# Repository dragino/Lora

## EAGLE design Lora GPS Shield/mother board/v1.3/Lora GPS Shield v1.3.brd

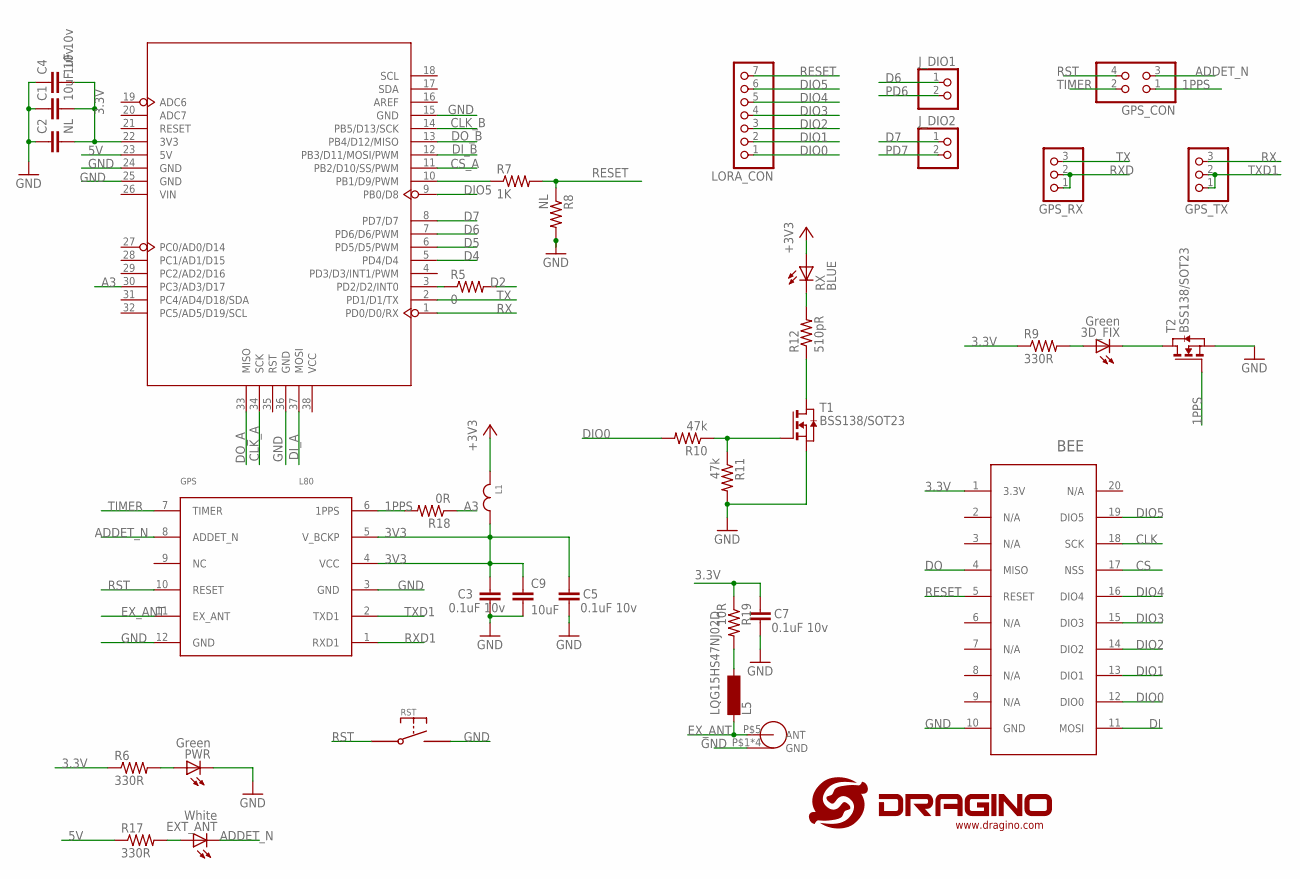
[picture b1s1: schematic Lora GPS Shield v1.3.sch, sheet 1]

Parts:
3D_FIX: Green; CHIPLED_0603
C1: 10uF 10v; C0805
C2: NL; C0402
C3, C5, C7: 0.1uF 10v; C0402
C4: 1uF 10v; C0402
C9: 10uF; C0805
EXT_ANT: White; DRAGINO_CHIPLED_0603
GPS: L80
GPS_ANT: NL; SMA-KE
GPS_CON: PINHD-2X2; 2X02
GPS_RX: PINHD-1X3; 1X03
GPS_TX: PINHD-1X3; 1X03
J_DIO1: PINHD-1X21X2_S; 1X02
J_DIO2: PINHD-1X2; 1X02
L1: JLC-PZ2012D800-3R0TF; C0805
L5: LQG15HS47NJ02D; L-0402
LORA_CON: PINHD-1X71X7_S; 1X07
PWR: Green; DRAGINO_CHIPLED_0603
R5: 0; R0402
R6, R9, R17: 330R; R0402
R7: 1K; R0402
R8: NL; R0402
R10, R11: 47k; R0402
R12: 510pR; R0402
R18: 0R; M0805
R19: 10R; R0402
RST: SWITCHTS-017; TS-017
RX: BLUE; CHIPLED_0603
T1, T2: BSS138/SOT23; SOT-23
U3: BEE; LORA
U5: MOUDLE_ARDUINO-38PMOUDLE_ARDUINO-38P_L; MOUDLE_ARDUINO-38P_L
U$1: LOGO-NEW; LOGO-SILK-NEW

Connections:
1PPS: GPS.6 (1PPS), GPS_CON.1, R18.2, T2.3 (G)
3.3V: C1.2, C2.2, C4.2, C7.2, L1.1, R6.1, R9.1, R19.1, RX.A, U3.1 (3.3V), U5.22 (3V3); also elsewhere on the board
3V3: C3.2, C5.2, C9.1, GPS.4 (VCC), GPS.5 (V_BCKP), L1.2
5V: R17.1, U5.23 (5V)
/RESET: R12.1, T1.1 (D)
A3: R18.1, U5.30 (PC3/AD3/D17)
ADDET_N: EXT_ANT.C, GPS.8 (ADDET_N), GPS_CON.3
CLK: U3.18 (SCK); also elsewhere on the board
CLK_A: U5.34 (SCK); also elsewhere on the board
CLK_B: U5.14 (PB5/D13/SCK); also elsewhere on the board
CS: U3.17 (NSS); also elsewhere on the board
CS_A: U5.11 (PB2/D10/SS/PWM); also elsewhere on the board
D2: R5.2; also elsewhere on the board
D4: U5.5 (PD4/D4); also elsewhere on the board
D5: U5.6 (PD5/D5/PWM); also elsewhere on the board
D6: J_DIO1.1, U5.7 (PD6/D6/PWM)
D7: J_DIO2.1, U5.8 (PD7/D7)
DI: U3.11 (MOSI); also elsewhere on the board
DIO0: LORA_CON.1, R10.2, U3.12 (DIO0); also elsewhere on the board
DIO1: LORA_CON.2, U3.13 (DIO1); also elsewhere on the board
DIO2: LORA_CON.3, U3.14 (DIO2); also elsewhere on the board
DIO3: LORA_CON.4, U3.15 (DIO3)
DIO4: LORA_CON.5, U3.16 (DIO4)
DIO5: LORA_CON.6, U3.19 (DIO5), U5.9 (PB0/D8)
DI_A: U5.37 (MOSI); also elsewhere on the board
DI_B: U5.12 (PB3/D11/MOSI/PWM); also elsewhere on the board
DO: U3.4 (MISO); also elsewhere on the board
DO_A: U5.33 (MISO); also elsewhere on the board
DO_B: U5.13 (PB4/D12/MISO); also elsewhere on the board
EX_ANT: GPS.11 (EX_ANT), GPS_ANT.P$5 (ANT), L5.1
GND: C1.1, C2.1, C3.1, C4.1, C5.1, C7.1, C9.2, GPS.3 (GND), GPS.12 (GND), GPS_ANT.P$1 (GND), GPS_ANT.P$2 (GND), GPS_ANT.P$3 (GND), GPS_ANT.P$4 (GND), PWR.C, R8.2, R11.2, RST.P$2, T1.2 (S), T2.2 (S), U3.10 (GND), U5.15 (GND), U5.24 (GND), U5.25 (GND), U5.36 (GND); also elsewhere on the board
unnamed: R5.1, U5.3 (PD2/D2/INT0)
unnamed: PWR.A, R6.2
unnamed: R7.1, U5.10 (PB1/D9/PWM)
unnamed: 3D_FIX.A, R9.2
unnamed: 3D_FIX.C, T2.1 (D)
unnamed: R10.1, R11.1, T1.3 (G)
unnamed: EXT_ANT.A, R17.2
unnamed: L5.2, R19.2
unnamed: R12.2, RX.C
PD6: J_DIO1.2; also elsewhere on the board
PD7: J_DIO2.2; also elsewhere on the board
RESET: LORA_CON.7, R7.2, R8.1, U3.5 (RESET)
RST: GPS.10 (RESET), GPS_CON.4, RST.P$1
RX: GPS_TX.3, U5.1 (PD0/D0/RX)
RXD: GPS_RX.1, GPS_RX.2; also elsewhere on the board
RXD1: GPS.1 (RXD1); also elsewhere on the board
TIMER: GPS.7 (TIMER), GPS_CON.2
TX: GPS_RX.3, U5.2 (PD1/D1/TX)
TXD1: GPS.2 (TXD1), GPS_TX.1, GPS_TX.2

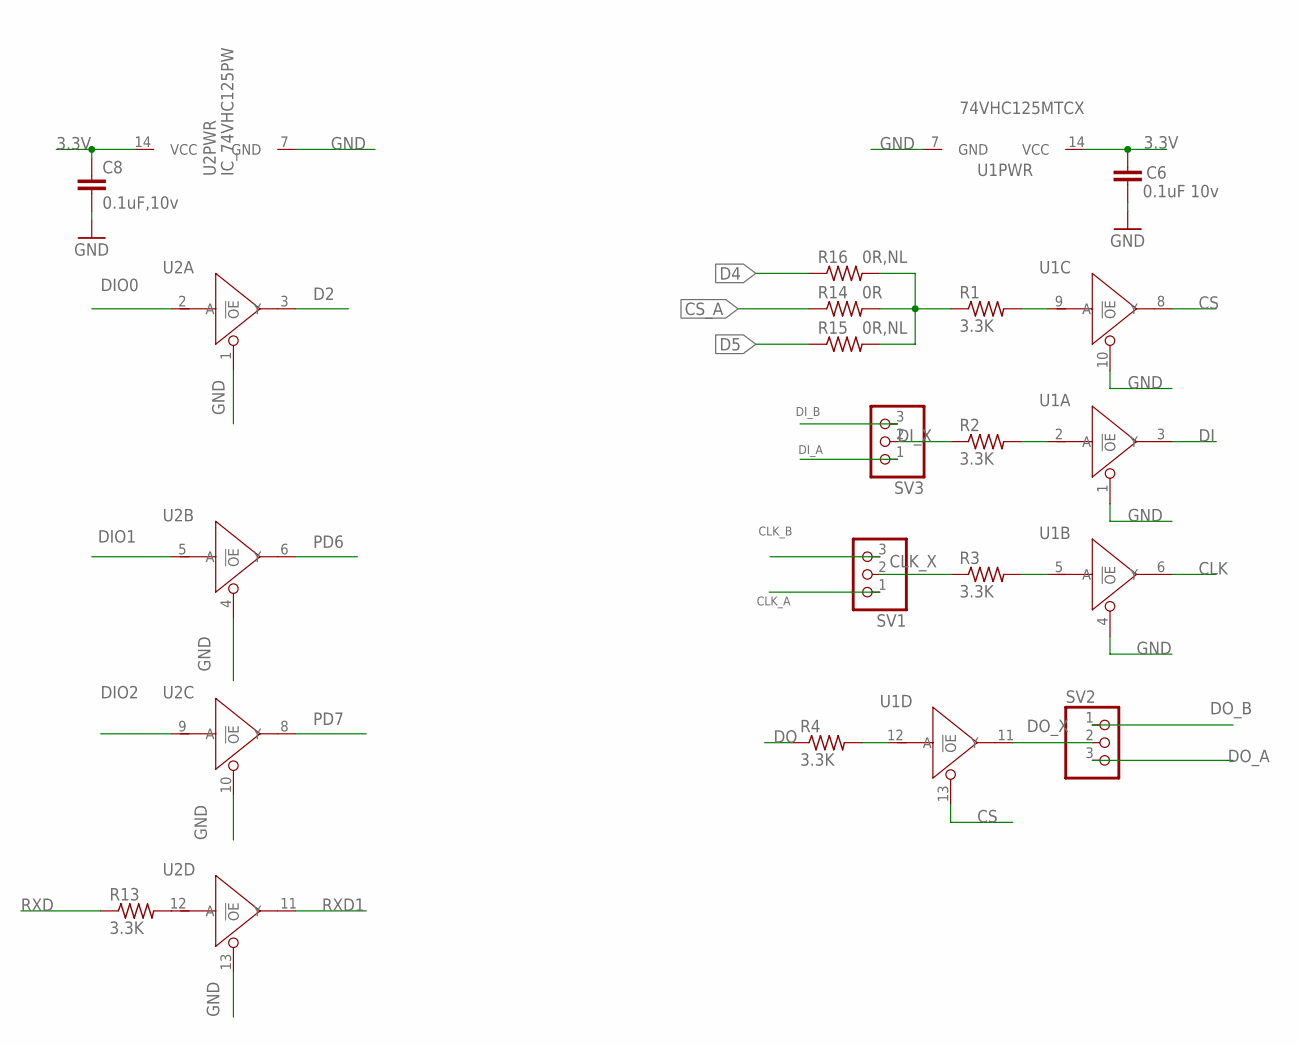
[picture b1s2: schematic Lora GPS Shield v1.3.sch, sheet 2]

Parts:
C6: 0.1uF 10v; C0402
C8: 0.1uF,10v; C0402
R1, R2, R3, R4, R13: 3.3K; R0402
R14: 0R; R0603
R15, R16: 0R,NL; R0603
SV1: PINHD-1X31X3_S; 1X03
SV2, SV3: PINHD-1X3; 1X03
U1: 74VHC125MTCX; TSSOP14
U2: IC_74VHC125PW; IC_TSSOP14

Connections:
3.3V: C6.2, C8.1, U1.14 (VCC), U2.14 (VCC); also elsewhere on the board
CLK: U1.6 (Y); also elsewhere on the board
CLK_A: SV1.1; also elsewhere on the board
CLK_B: SV1.3; also elsewhere on the board
CLK_X: R3.1, SV1.2
CS: U1.8 (Y), U1.13 (!OE); also elsewhere on the board
CS_A: R14.1; also elsewhere on the board
D2: U2.3 (Y); also elsewhere on the board
D4: R16.1; also elsewhere on the board
D5: R15.1; also elsewhere on the board
DI: U1.3 (Y); also elsewhere on the board
DIO0: U2.2 (A); also elsewhere on the board
DIO1: U2.5 (A); also elsewhere on the board
DIO2: U2.9 (A); also elsewhere on the board
DI_A: SV3.1; also elsewhere on the board
DI_B: SV3.3; also elsewhere on the board
DI_X: R2.1, SV3.2
DO: R4.1; also elsewhere on the board
DO_A: SV2.3; also elsewhere on the board
DO_B: SV2.1; also elsewhere on the board
DO_X: SV2.2, U1.11 (Y)
GND: C6.1, C8.2, U1.1 (!OE), U1.4 (!OE), U1.7 (GND), U1.10 (!OE), U2.1 (!OE), U2.4 (!OE), U2.7 (GND), U2.10 (!OE), U2.13 (!OE); also elsewhere on the board
unnamed: R4.2, U1.12 (A)
unnamed: R3.2, U1.5 (A)
unnamed: R2.2, U1.2 (A)
unnamed: R1.2, U1.9 (A)
unnamed: R13.2, U2.12 (A)
unnamed: R1.1, R14.2, R15.2, R16.2
PD6: U2.6 (Y); also elsewhere on the board
PD7: U2.8 (Y); also elsewhere on the board
RXD: R13.1; also elsewhere on the board
RXD1: U2.11 (Y); also elsewhere on the board

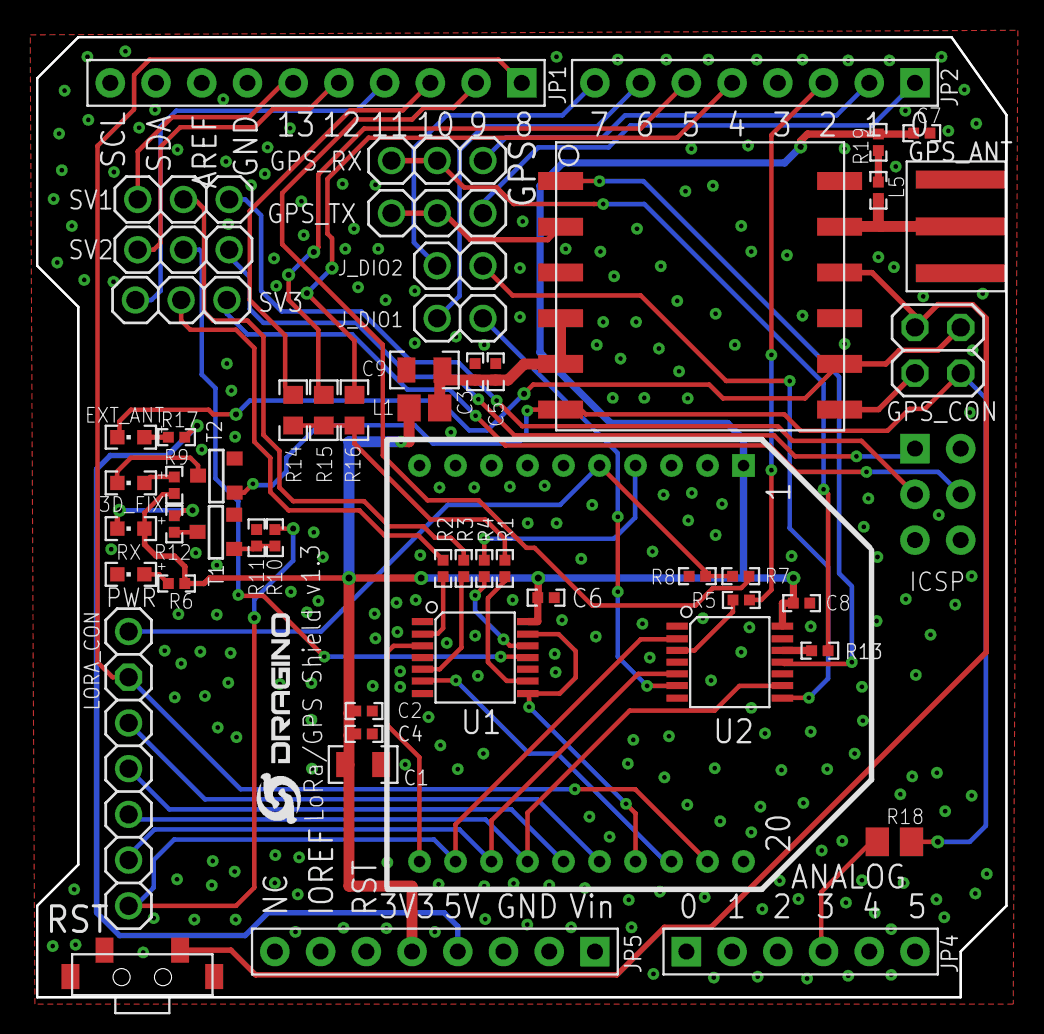
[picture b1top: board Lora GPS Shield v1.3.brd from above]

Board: 2 copper layers, 53.8 x 53.3 mm, 53 parts (0 on the bottom side), 59 nets.

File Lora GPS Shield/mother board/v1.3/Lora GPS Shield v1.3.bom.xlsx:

LoRa GPS Shield v1.3
Part | Value | Device
3D_FIX | Green | LEDCHIPLED_0603
C1 | 10uF 10v | C-EUC0805
C2 | NL | C-EUC0402
C3 | 0.1uF 10v | C-EUC0402
C4 | 1uF 10v | C-EUC0402
C5 | 0.1uF 10v | C-EUC0402
C6 | 0.1uF 10v | C-EUC0402
C7 | 0.1uF 10v | C-EUC0402
C8 | 0.1uF 10v | C-EUC0402
C9 | 10uF | C-EUC0805
EXT_ANT | White | DRAGINO_LEDCHIPLED_0603
GPS | L80 | L80
GPS_ANT | NL | SMA-KE
GPS_CON |  | PINHD-2X2
GPS_RX |  | PINHD-1X3
GPS_TX |  | PINHD-1X3
J_DIO1 |  | PINHD-1X21X2_S
J_DIO2 |  | PINHD-1X2
L1 | JLC-PZ2012D800-3R0TF | BEADS0805
L5 | LQG15HS47NJ02D | L
LORA_CON |  | PINHD-1X71X7_S
PWR | Green | DRAGINO_LEDCHIPLED_0603
R1 | 3.3K | R-US_R0402
R2 | 3.3K | R-US_R0402
R3 | 3.3K | R-US_R0402
R4 | 3.3K | R-US_R0402
R5 | 0 | R-US_R0402
R6 | 330R | R-US_R0402
R7 | 1K | R-US_R0402
R8 | NL | R-US_R0402
R9 | 330R | R-US_R0402
R10 | 47k | R-US_R0402
R11 | 47k | R-US_R0402
R12 | 510pR | R-US_R0402
R13 | 3.3K | R-US_R0402
R14 | 0R | R-US_R0603
R15 | 0R NL | R-US_R0603
R16 | 0R NL | R-US_R0603
R17 | 330R | R-US_R0402
R18 | 0R | R-US_M0805
R19 | 10R | R-US_R0402
RST | SWITCHTS-017 | SWITCHTS-017
RX | BLUE | LEDCHIPLED_0603
SV1 |  | PINHD-1X31X3_S
SV2 |  | PINHD-1X3
SV3 |  | PINHD-1X3
T1 | BSS138/SOT23 | NMOSFET-SOT23
T2 | BSS138/SOT23 | NMOSFET-SOT23
U$1 | LOGO-NEW | LOGO-NEW
U1 | 74VHC125MTCX | 74VHC125PW
U2 | IC_74VHC125PW | IC_74VHC125PW
U3 | BEE | LORAHAT_S
U5 |  | MOUDLE_ARDUINO-38PMOUDLE_ARDUINO-38P_L

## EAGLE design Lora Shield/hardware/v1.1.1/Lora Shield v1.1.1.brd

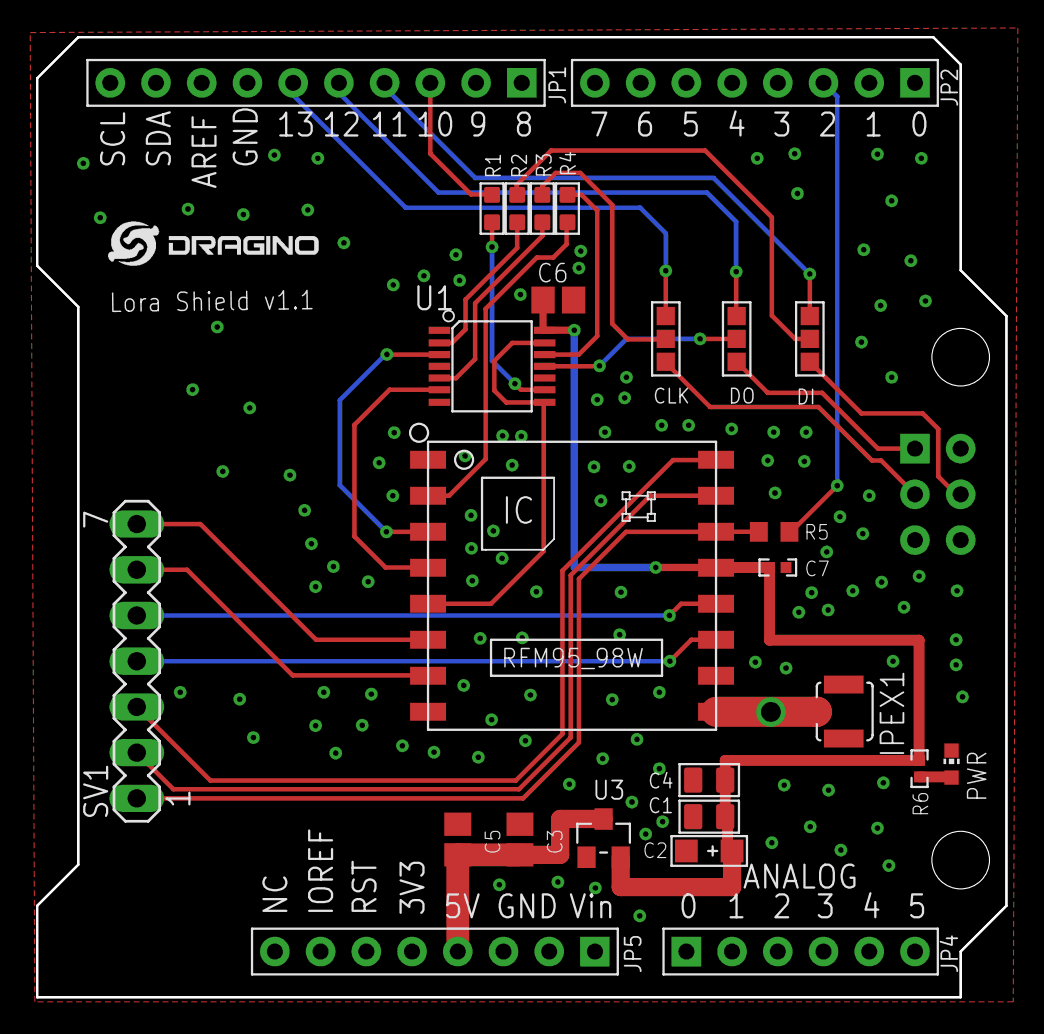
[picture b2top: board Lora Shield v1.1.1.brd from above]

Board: 2 copper layers, 53.8 x 53.3 mm, 24 parts (0 on the bottom side), 31 nets.

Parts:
C1: 10uF 10v; C0805
C2: DNP; AVX-A
C3: 10uF,10v; C0805
C4: 1uF 10v; C0805
C5, C6: 0.1uF 10v; C0805
C7: 0.1uF 10V; C0402
CLK: 3P-SMD-4.1X1.5
DI: 3P-SMD-4.1X1.5
DO: 3P-SMD-4.1X1.5
IPEX1: I-PEX
PWR: Green; CHIP-LED0603
R1, R2, R3, R4: 3.3K; R0603
R5: 0; R0603
R6: 330R; R0402
SV1: MA07-1
U1: 74VHC125MTCX; TSSOP14
U3: XC6206P332MR-G; SOT23
U4: RFM92_93W
U5: MOUDLE_ARDUINO-328P_S
U$1: LOGO-NEW; LOGO-SILK-NEW

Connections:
3V3: C1.2, C2.+, C4.2, C6.2, C7.2, R6.1, U1.14, U3.2, U4.13
5V: C3.2, C5.2, U3.3, U5.23
ANT: IPEX1.SIG, U4.9
CLK: U1.6, U4.4
CLK_A: CLK.00, U5.34
CLK_B: CLK.11, U5.14
CLK_X: CLK.MM, R3.1
CS: U1.8, U1.13, U4.5
CS_A: R1.1, U5.11
DI: U1.3, U4.3
DIO0: R5.2, SV1.1, U4.14
DIO1: SV1.2, U4.15
DIO2: SV1.3, U4.16
DIO3: SV1.4, U4.11
DIO4: SV1.5, U4.12
DIO5: SV1.6, U4.7
DI_A: DI.00, U5.37
DI_B: DI.11, U5.12
DI_X: DI.MM, R2.1
DO: R4.1, U4.2
DO_A: DO.11, U5.33
DO_B: DO.00, U5.13
DO_X: DO.MM, U1.11
GND: C1.1, C2.-, C3.1, C4.1, C5.1, C6.1, C7.1, IPEX1.GND, IPEX1.GND1, PWR.C, U1.1, U1.4, U1.7, U1.10, U3.1, U4.1, U4.8, U4.10, U5.15, U5.24, U5.25, U5.36
unnamed: R5.1, U5.3
unnamed: R4.2, U1.12
unnamed: R3.2, U1.5
unnamed: R2.2, U1.2
unnamed: R1.2, U1.9
unnamed: PWR.A, R6.2
RESET: SV1.7, U4.6

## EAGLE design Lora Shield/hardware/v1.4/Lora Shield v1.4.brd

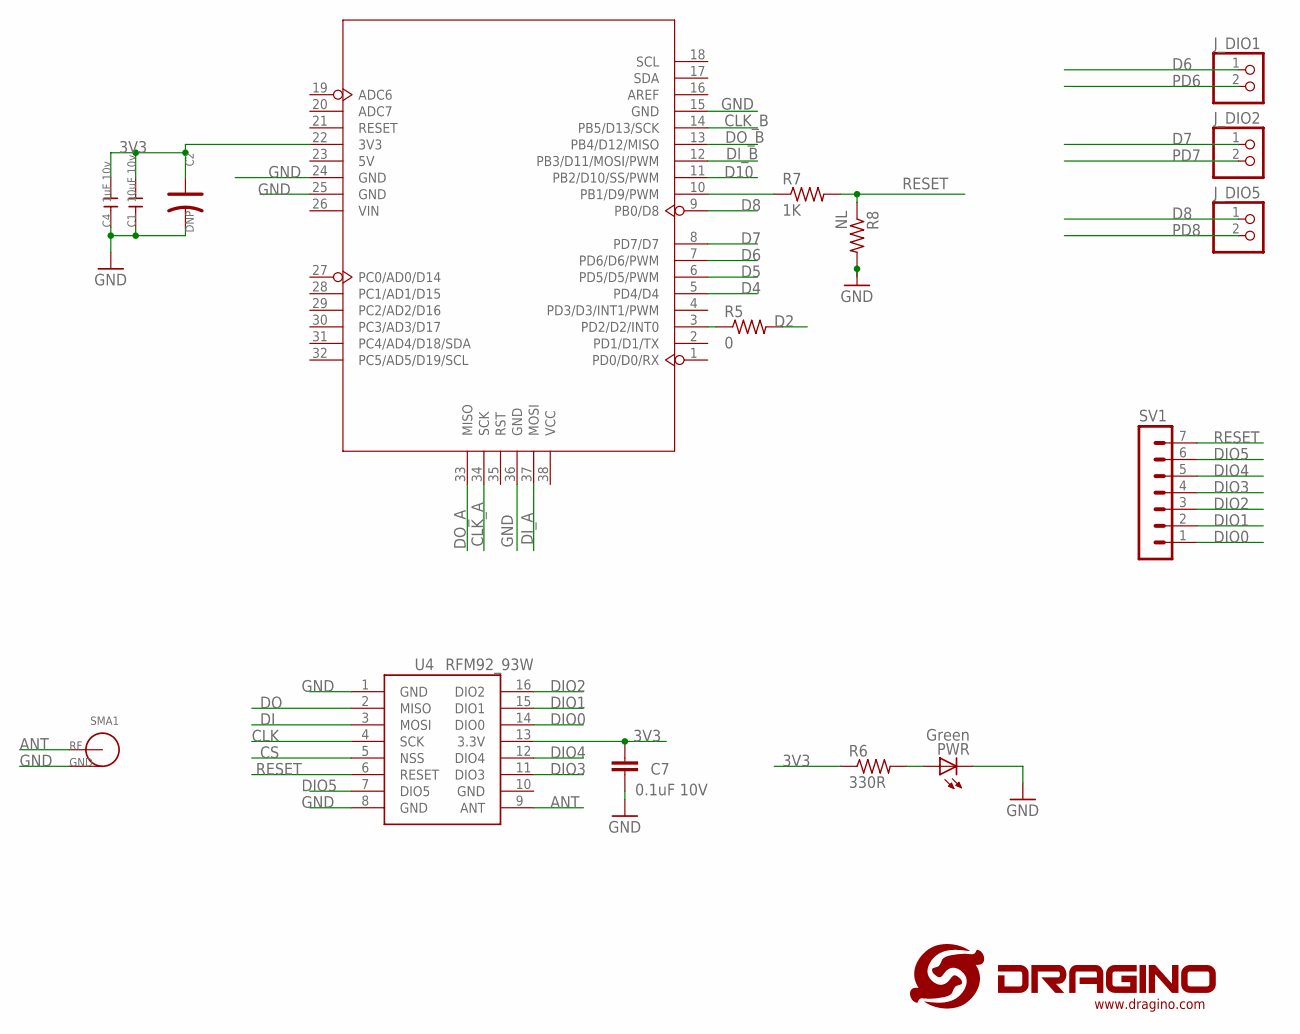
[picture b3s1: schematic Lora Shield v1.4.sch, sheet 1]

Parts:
C1: 10uF 10v; C0805
C2: DNP; AVX-A
C4: 1uF 10v; C0805
C7: 0.1uF 10V; C0402
J_DIO1, J_DIO2, J_DIO5: PINHD-1X2; 1X02
PWR: Green; CHIP-LED0603
R5: 0; R0603
R6: 330R; R0402
R7: 1K; R0402
R8: NL; R0402
SMA1: SMA-KWE
SV1: MA07-1
U4: RFM92_93W
U5: MOUDLE_ARDUINO-38P328P_NO_VIA; MOUDLE_ARDUINO-328P--
U$1: LOGO-NEW; LOGO-SILK-NEW

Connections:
3V3: C1.2, C2.+, C4.2, C7.2, R6.1, U4.13 (3.3V), U5.22 (3V3); also elsewhere on the board
ANT: SMA1.1 (SIG), U4.9 (ANT)
CLK: U4.4 (SCK); also elsewhere on the board
CLK_A: U5.34 (SCK); also elsewhere on the board
CLK_B: U5.14 (PB5/D13/SCK); also elsewhere on the board
CS: U4.5 (NSS); also elsewhere on the board
D2: R5.2; also elsewhere on the board
D4: U5.5 (PD4/D4); also elsewhere on the board
D5: U5.6 (PD5/D5/PWM); also elsewhere on the board
D6: J_DIO1.1, U5.7 (PD6/D6/PWM)
D7: J_DIO2.1, U5.8 (PD7/D7)
D8: J_DIO5.1, U5.9 (PB0/D8)
D10: U5.11 (PB2/D10/SS/PWM); also elsewhere on the board
DI: U4.3 (MOSI); also elsewhere on the board
DIO0: SV1.1, U4.14 (DIO0); also elsewhere on the board
DIO1: SV1.2, U4.15 (DIO1); also elsewhere on the board
DIO2: SV1.3, U4.16 (DIO2); also elsewhere on the board
DIO3: SV1.4, U4.11 (DIO3)
DIO4: SV1.5, U4.12 (DIO4)
DIO5: SV1.6, U4.7 (DIO5); also elsewhere on the board
DI_A: U5.37 (MOSI); also elsewhere on the board
DI_B: U5.12 (PB3/D11/MOSI/PWM); also elsewhere on the board
DO: U4.2 (MISO); also elsewhere on the board
DO_A: U5.33 (MISO); also elsewhere on the board
DO_B: U5.13 (PB4/D12/MISO); also elsewhere on the board
GND: C1.1, C2.-, C4.1, C7.1, PWR.C, R8.2, SMA1.2 (GND), SMA1.3 (GND), SMA1.4 (GND), SMA1.5 (GND), U4.1 (GND), U4.8 (GND), U4.10 (GND), U5.15 (GND), U5.24 (GND), U5.25 (GND), U5.36 (GND); also elsewhere on the board
unnamed: R5.1, U5.3 (PD2/D2/INT0)
unnamed: PWR.A, R6.2
unnamed: R7.1, U5.10 (PB1/D9/PWM)
PD6: J_DIO1.2; also elsewhere on the board
PD7: J_DIO2.2; also elsewhere on the board
PD8: J_DIO5.2; also elsewhere on the board
RESET: R7.2, R8.1, SV1.7, U4.6 (RESET)

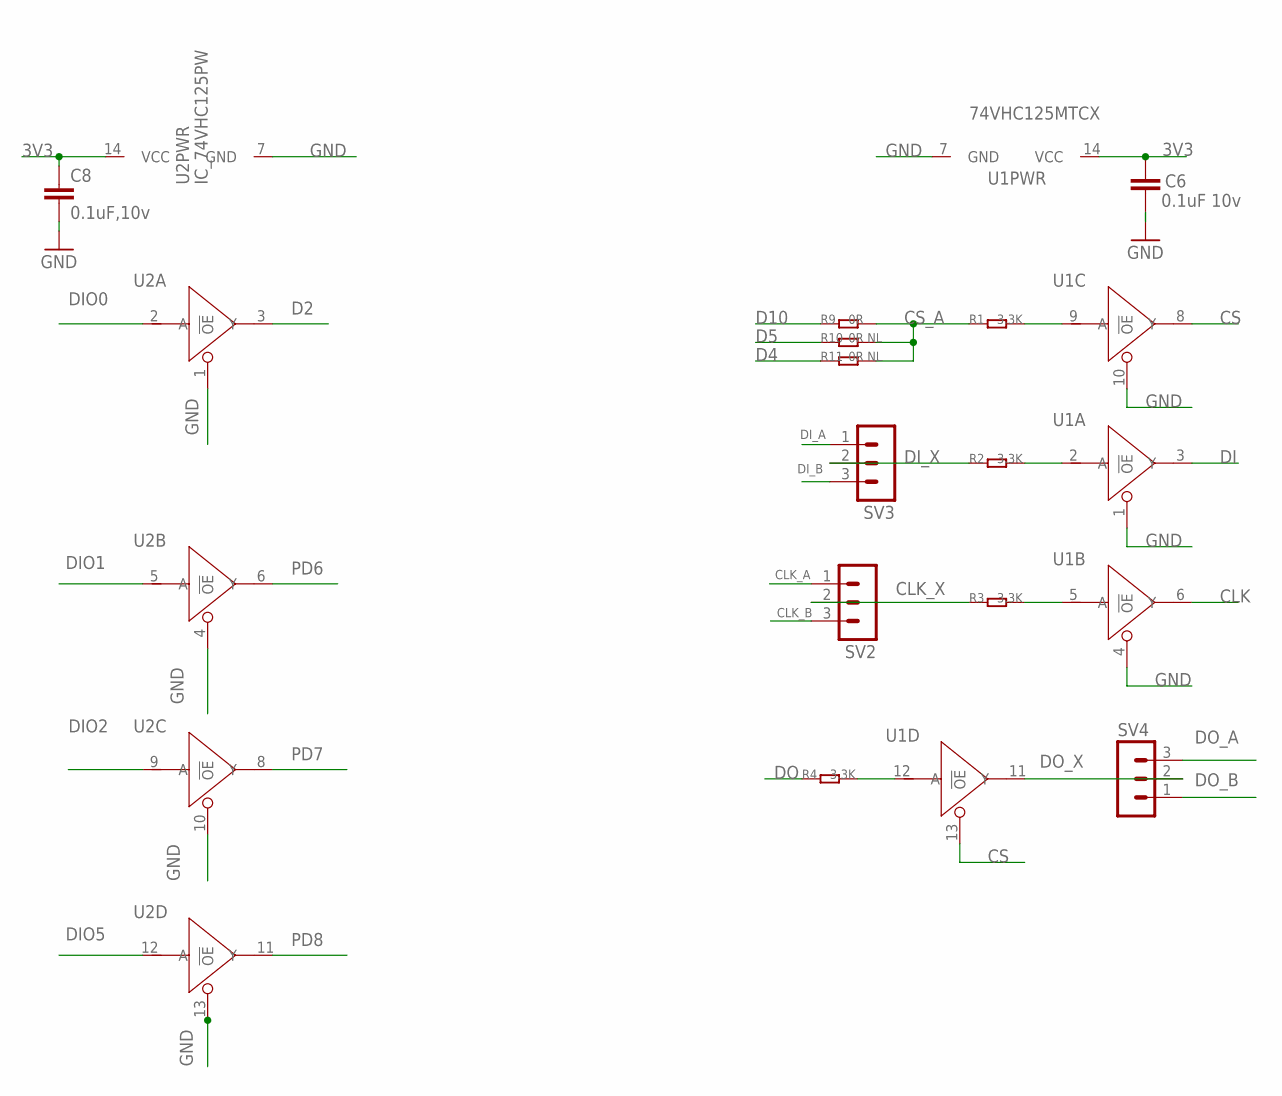
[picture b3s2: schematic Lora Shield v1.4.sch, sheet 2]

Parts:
C6: 0.1uF 10v; C0805
C8: 0.1uF,10v; C0805
R1, R2, R3, R4: 3.3K; R0603
R9: 0R; R0603
R10, R11: 0R NL; R0603
SV2, SV3, SV4: MA03-1
U1: 74VHC125MTCX; TSSOP14
U2: IC_74VHC125PW; IC_TSSOP14

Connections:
3V3: C6.2, C8.1, U1.14 (VCC), U2.14 (VCC); also elsewhere on the board
CLK: U1.6 (Y); also elsewhere on the board
CLK_A: SV2.1; also elsewhere on the board
CLK_B: SV2.3; also elsewhere on the board
CLK_X: R3.1, SV2.2
CS: U1.8 (Y), U1.13 (!OE); also elsewhere on the board
CS_A: R1.1, R9.2, R10.2, R11.2
D2: U2.3 (Y); also elsewhere on the board
D4: R11.1; also elsewhere on the board
D5: R10.1; also elsewhere on the board
D10: R9.1; also elsewhere on the board
DI: U1.3 (Y); also elsewhere on the board
DIO0: U2.2 (A); also elsewhere on the board
DIO1: U2.5 (A); also elsewhere on the board
DIO2: U2.9 (A); also elsewhere on the board
DIO5: U2.12 (A); also elsewhere on the board
DI_A: SV3.1; also elsewhere on the board
DI_B: SV3.3; also elsewhere on the board
DI_X: R2.1, SV3.2
DO: R4.1; also elsewhere on the board
DO_A: SV4.3; also elsewhere on the board
DO_B: SV4.1; also elsewhere on the board
DO_X: SV4.2, U1.11 (Y)
GND: C6.1, C8.2, U1.1 (!OE), U1.4 (!OE), U1.7 (GND), U1.10 (!OE), U2.1 (!OE), U2.4 (!OE), U2.7 (GND), U2.10 (!OE), U2.13 (!OE); also elsewhere on the board
unnamed: R4.2, U1.12 (A)
unnamed: R3.2, U1.5 (A)
unnamed: R2.2, U1.2 (A)
unnamed: R1.2, U1.9 (A)
PD6: U2.6 (Y); also elsewhere on the board
PD7: U2.8 (Y); also elsewhere on the board
PD8: U2.11 (Y); also elsewhere on the board

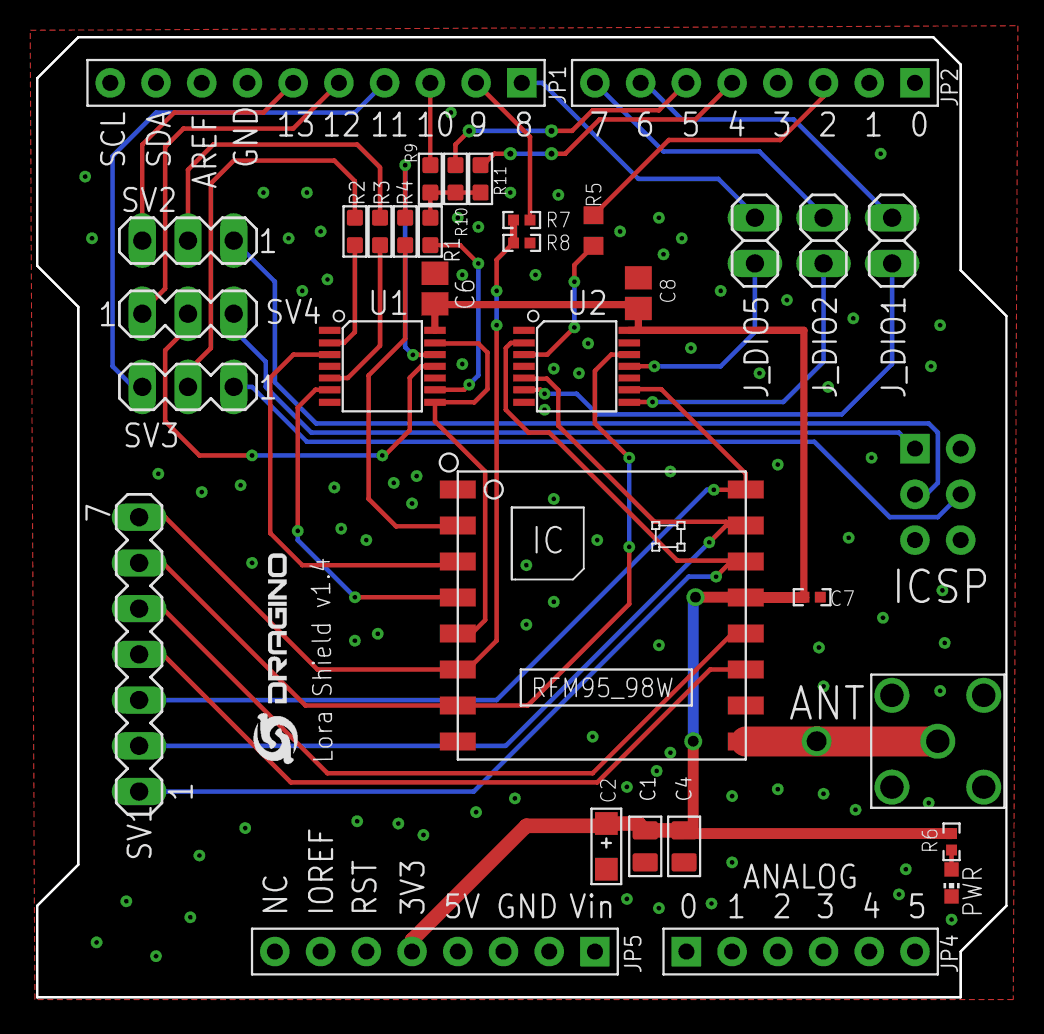
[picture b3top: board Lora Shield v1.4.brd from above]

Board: 2 copper layers, 53.8 x 53.3 mm, 31 parts (0 on the bottom side), 41 nets.

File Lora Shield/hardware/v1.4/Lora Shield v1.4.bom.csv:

"Part","Value","Device","Package","Description","MF","MPN","OC_FARNELL","OC_NEWARK",
"C1","10uF 10v","C-0805","C0805","Ceramic Capacitors","","","","",
"C2","DNP","CAP-AVX-A","AVX-A","Electrolytic Capacitors Tantalum Capacitors and Super Capacitors","","","","",
"C4","1uF 10v","C-0805","C0805","Ceramic Capacitors","","","","",
"C6","0.1uF 10v","C-EUC0805","C0805","CAPACITOR  European symbol","","","","",
"C7","0.1uF 10V","C-EUC0402","C0402","CAPACITOR  European symbol","","","","",
"C8","0.1uF 10v","C-EUC0805","C0805","CAPACITOR  European symbol","","","","",
"J_DIO1","","PINHD-1X2","1X02","PIN HEADER","","","","",
"J_DIO2","","PINHD-1X2","1X02","PIN HEADER","","","","",
"J_DIO5","","PINHD-1X2","1X02","PIN HEADER","","","","",
"PWR","Green","LEDCHIP-LED0603","CHIP-LED0603","LED","","","","",
"R1","3.3K","R-0603","R0603","","","","","",
"R2","3.3K","R-0603","R0603","","","","","",
"R3","3.3K","R-0603","R0603","","","","","",
"R4","3.3K","R-0603","R0603","","","","","",
"R5","0","R-US_R0603","R0603","RESISTOR  American symbol","","","","",
"R6","330R","R-US_R0402","R0402","RESISTOR  American symbol","","","","",
"R7","1K","R-US_R0402","R0402","RESISTOR  American symbol","","","","",
"R8","NL","R-US_R0402","R0402","RESISTOR  American symbol","","","","",
"R9","0R","R-0603","R0603","","","","","",
"R10","0R NL","R-0603","R0603","","","","","",
"R11","0R NL","R-0603","R0603","","","","","",
"SMA1","SMA-KWE","SMA-KWE","SMA-KWE","","","","","",
"SV1","","MA07-1","MA07-1","PIN HEADER","","","unknown","unknown",
"SV2","","MA03-1","MA03-1","PIN HEADER","","","unknown","unknown",
"SV3","","MA03-1","MA03-1","PIN HEADER","","","unknown","unknown",
"SV4","","MA03-1","MA03-1","PIN HEADER","","","unknown","unknown",
"U$1","LOGO-NEW","LOGO-NEW","LOGO-SILK-NEW","","","","","",
"U1","74VHC125MTCX","74VHC125PW","TSSOP14","Quad Buffer/Line Driver,3-state","","","","",
"U2","IC_74VHC125PW","IC_74VHC125PW","IC_TSSOP14","Quad Buffer/Line Driver,3-state","","","","",
"U4","RFM92_93W","RFM92_93W","RFM92_93W","","","","","",
"U5","","MOUDLE_ARDUINO-38P328P_NO_VIA","MOUDLE_ARDUINO-328P--","","","","","",

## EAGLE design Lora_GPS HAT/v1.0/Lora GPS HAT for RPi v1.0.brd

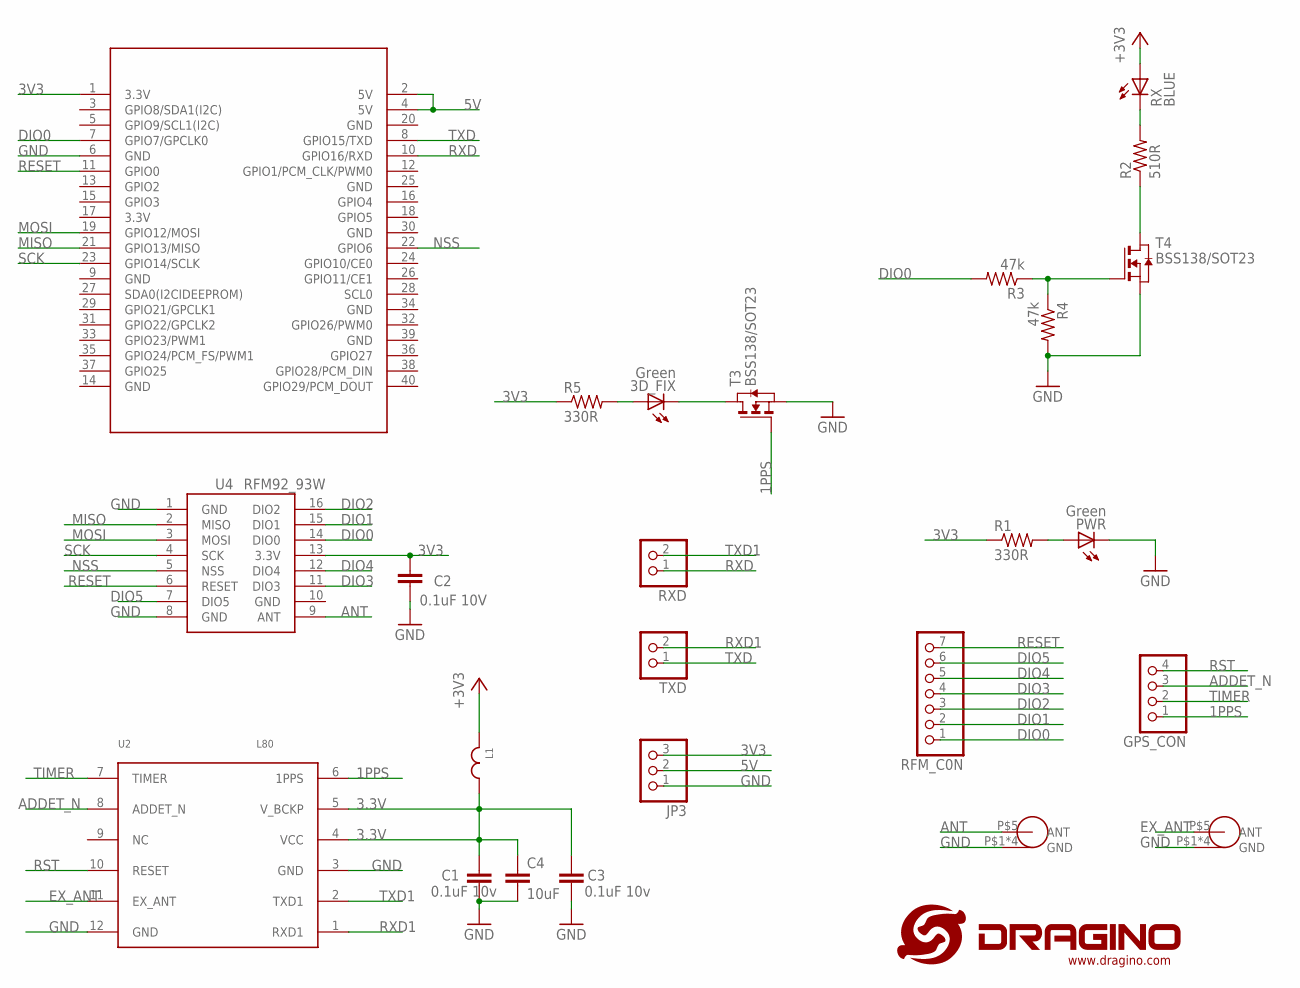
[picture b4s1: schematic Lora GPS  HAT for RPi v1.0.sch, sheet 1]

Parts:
3D_FIX: Green; CHIPLED_0603
C1, C3: 0.1uF 10v; C0805
C2: 0.1uF 10V; C0402
C4: 10uF; C1206K
GPS_ANT: NL; SMA-KE
GPS_CON: PINHD-1X4; 1X04
JP3: PINHD-1X3; 1X03
L1: JLC-PZ2012D800-3R0TF; C0805
LORA_ANT: SMA-KE
PWR: Green; CHIPLED_0603
R1, R5: 330R; R0402
R2: 510R; R0402
R3, R4: 47k; R0402
RFM_C0N: PINHD-1X7; 1X07
RX: BLUE; CHIPLED_0603
RXD: PINHD-1X2; 1X02
T3, T4: BSS138/SOT23; SOT-23
TXD: PINHD-1X2; 1X02
U2: L80
U4: RFM92_93W
U$1: LOGO-NEW; LOGO-SILK-NEW
U$2: RPILORASHIELD

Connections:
1PPS: GPS_CON.1, T3.3 (G), U2.6 (1PPS)
3.3V: C1.2, C3.2, C4.1, L1.2, U2.4 (VCC), U2.5 (V_BCKP)
3V3: C2.2, JP3.3, L1.1, R1.1, R5.1, RX.A, U4.13 (3.3V), U$2.1 (3.3V)
5V: JP3.2, U$2.2 (5V), U$2.4 (5V)
/RESET: R2.1, T4.1 (D)
ADDET_N: GPS_CON.3, U2.8 (ADDET_N)
ANT: LORA_ANT.P$5 (ANT), U4.9 (ANT)
DIO0: R3.2, RFM_C0N.1, U4.14 (DIO0), U$2.7 (GPIO7/GPCLK0)
DIO1: RFM_C0N.2, U4.15 (DIO1)
DIO2: RFM_C0N.3, U4.16 (DIO2)
DIO3: RFM_C0N.4, U4.11 (DIO3)
DIO4: RFM_C0N.5, U4.12 (DIO4)
DIO5: RFM_C0N.6, U4.7 (DIO5)
EX_ANT: GPS_ANT.P$5 (ANT), U2.11 (EX_ANT)
GND: C1.1, C2.1, C3.1, C4.2, GPS_ANT.P$1 (GND), GPS_ANT.P$2 (GND), GPS_ANT.P$3 (GND), GPS_ANT.P$4 (GND), JP3.1, LORA_ANT.P$1 (GND), LORA_ANT.P$2 (GND), LORA_ANT.P$3 (GND), LORA_ANT.P$4 (GND), PWR.C, R4.2, T3.2 (S), T4.2 (S), U2.3 (GND), U2.12 (GND), U4.1 (GND), U4.8 (GND), U4.10 (GND), U$2.6 (GND)
MISO: U4.2 (MISO), U$2.21 (GPIO13/MISO)
MOSI: U4.3 (MOSI), U$2.19 (GPIO12/MOSI)
unnamed: R3.1, R4.1, T4.3 (G)
unnamed: 3D_FIX.A, R5.2
unnamed: 3D_FIX.C, T3.1 (D)
unnamed: PWR.A, R1.2
unnamed: R2.2, RX.C
NSS: U4.5 (NSS), U$2.22 (GPIO6)
RESET: RFM_C0N.7, U4.6 (RESET), U$2.11 (GPIO0)
RST: GPS_CON.4, U2.10 (RESET)
RXD: RXD.1, U$2.10 (GPIO16/RXD)
RXD1: TXD.2, U2.1 (RXD1)
SCK: U4.4 (SCK), U$2.23 (GPIO14/SCLK)
TIMER: GPS_CON.2, U2.7 (TIMER)
TXD: TXD.1, U$2.8 (GPIO15/TXD)
TXD1: RXD.2, U2.2 (TXD1)

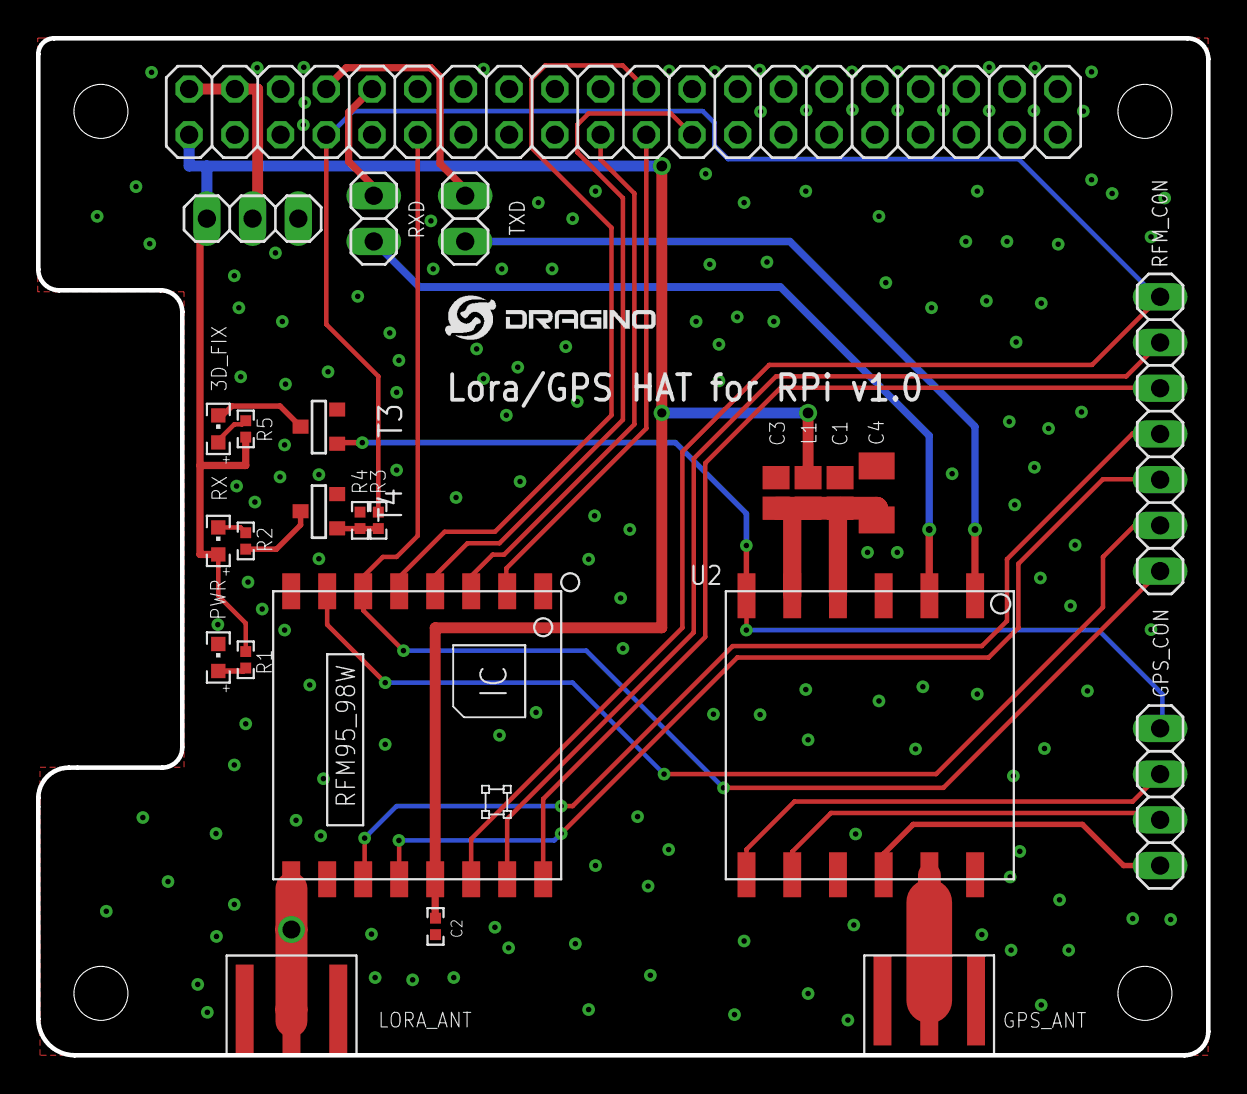
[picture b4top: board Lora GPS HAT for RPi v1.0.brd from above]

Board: 2 copper layers, 65.0 x 56.5 mm, 26 parts (0 on the bottom side), 31 nets.

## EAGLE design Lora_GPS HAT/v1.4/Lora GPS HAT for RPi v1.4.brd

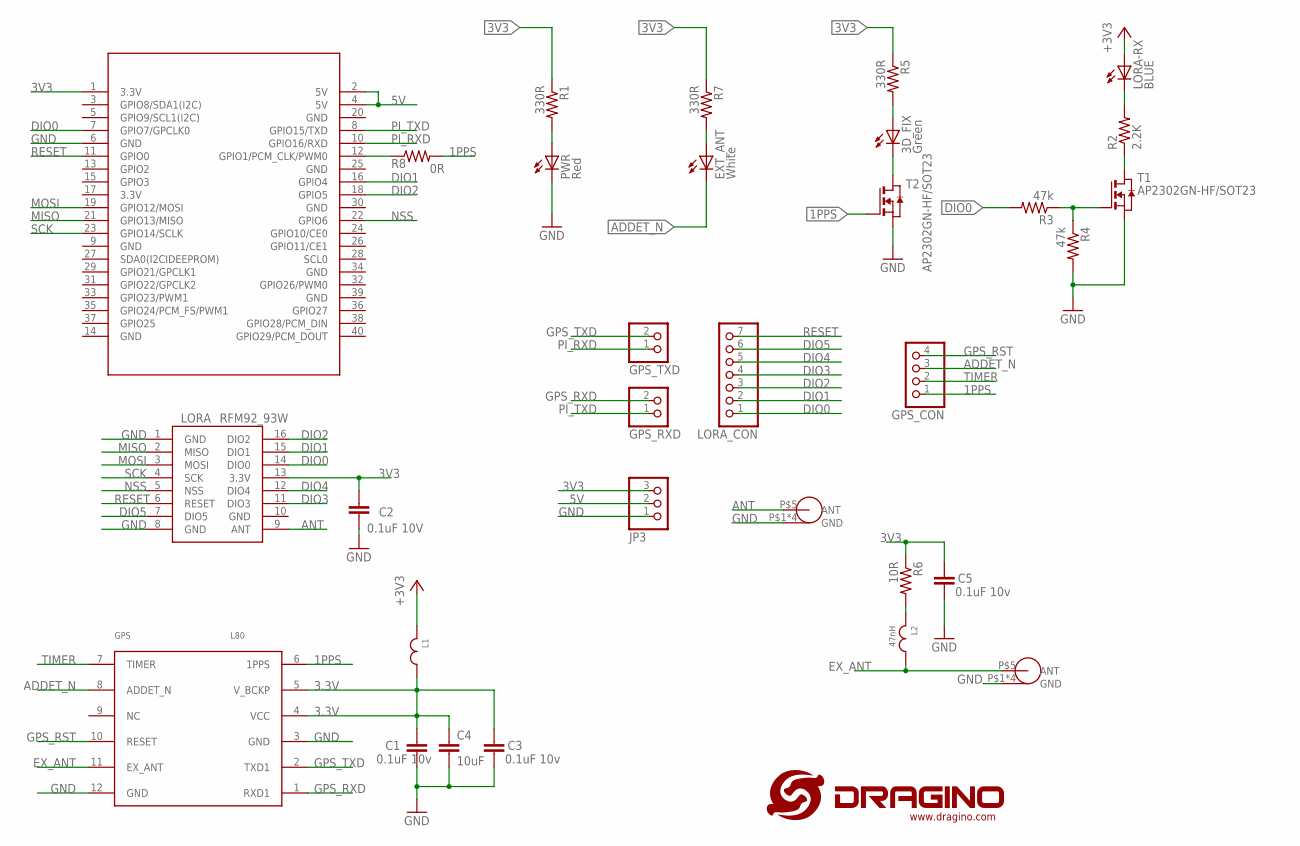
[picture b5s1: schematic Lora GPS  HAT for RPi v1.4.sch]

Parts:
3D_FIX: Green; CHIPLED_0603
C1, C3, C5: 0.1uF 10v; C0402
C2: 0.1uF 10V; C0402
C4: 10uF; C1206K
EXT_ANT: White; CHIPLED_0603
GPS: L80
GPS_ANT: NL; SMA-KE
GPS_CON: PINHD-1X4; 1X04
GPS_RXD: PINHD-1X2; 1X02
GPS_TXD: PINHD-1X2; 1X02
JP3: PINHD-1X3; 1X03
L1: JLC-PZ2012D800-3R0TF; C0805
L2: 47nH; C0402
LORA: RFM92_93W
LORA-RX: BLUE; CHIPLED_0603
LORA_ANT: SMA-KE
LORA_CON: PINHD-1X7; 1X07
PWR: Red; CHIPLED_0603
R1, R5, R7: 330R; R0402
R2: 2.2K; R0402
R3, R4: 47k; R0402
R6: 10R; R0402
R8: 0R; R0805
T1, T2: AP2302GN-HF/SOT23; SOT-23
U$1: LOGO-NEW; LOGO-SILK-NEW
U$2: RPILORASHIELD

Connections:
1PPS: GPS.6 (1PPS), GPS_CON.1, R8.2, T2.3 (G)
3.3V: C1.2, C3.2, C4.1, GPS.4 (VCC), GPS.5 (V_BCKP), L1.2
3V3: C2.2, C5.2, JP3.3, L1.1, LORA.13 (3.3V), LORA-RX.A, R1.1, R5.1, R6.1, R7.1, U$2.1 (3.3V)
5V: JP3.2, U$2.2 (5V), U$2.4 (5V)
/RESET: R2.1, T1.1 (D)
ADDET_N: EXT_ANT.C, GPS.8 (ADDET_N), GPS_CON.3
ANT: LORA.9 (ANT), LORA_ANT.P$5 (ANT)
DIO0: LORA.14 (DIO0), LORA_CON.1, R3.2, U$2.7 (GPIO7/GPCLK0)
DIO1: LORA.15 (DIO1), LORA_CON.2, U$2.16 (GPIO4)
DIO2: LORA.16 (DIO2), LORA_CON.3, U$2.18 (GPIO5)
DIO3: LORA.11 (DIO3), LORA_CON.4
DIO4: LORA.12 (DIO4), LORA_CON.5
DIO5: LORA.7 (DIO5), LORA_CON.6
EX_ANT: GPS.11 (EX_ANT), GPS_ANT.P$5 (ANT), L2.2
GND: C1.1, C2.1, C3.1, C4.2, C5.1, GPS.3 (GND), GPS.12 (GND), GPS_ANT.P$1 (GND), GPS_ANT.P$2 (GND), GPS_ANT.P$3 (GND), GPS_ANT.P$4 (GND), JP3.1, LORA.1 (GND), LORA.8 (GND), LORA.10 (GND), LORA_ANT.P$1 (GND), LORA_ANT.P$2 (GND), LORA_ANT.P$3 (GND), LORA_ANT.P$4 (GND), PWR.C, R4.2, T1.2 (S), T2.2 (S), U$2.6 (GND)
GPS_RST: GPS.10 (RESET), GPS_CON.4
GPS_RXD: GPS.1 (RXD1), GPS_RXD.2
GPS_TXD: GPS.2 (TXD1), GPS_TXD.2
MISO: LORA.2 (MISO), U$2.21 (GPIO13/MISO)
MOSI: LORA.3 (MOSI), U$2.19 (GPIO12/MOSI)
unnamed: R3.1, R4.1, T1.3 (G)
unnamed: 3D_FIX.A, R5.2
unnamed: 3D_FIX.C, T2.1 (D)
unnamed: L2.1, R6.2
unnamed: EXT_ANT.A, R7.2
unnamed: PWR.A, R1.2
unnamed: R8.1, U$2.12 (GPIO1/PCM_CLK/PWM0)
unnamed: LORA-RX.C, R2.2
NSS: LORA.5 (NSS), U$2.22 (GPIO6)
PI_RXD: GPS_TXD.1, U$2.10 (GPIO16/RXD)
PI_TXD: GPS_RXD.1, U$2.8 (GPIO15/TXD)
RESET: LORA.6 (RESET), LORA_CON.7, U$2.11 (GPIO0)
SCK: LORA.4 (SCK), U$2.23 (GPIO14/SCLK)
TIMER: GPS.7 (TIMER), GPS_CON.2

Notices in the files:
parts and their libraries:
dragino: http://creativecommons.org/licenses/by-sa/3.0
dragino: Released under the CC Attribution Share-Alike 3.0 License
